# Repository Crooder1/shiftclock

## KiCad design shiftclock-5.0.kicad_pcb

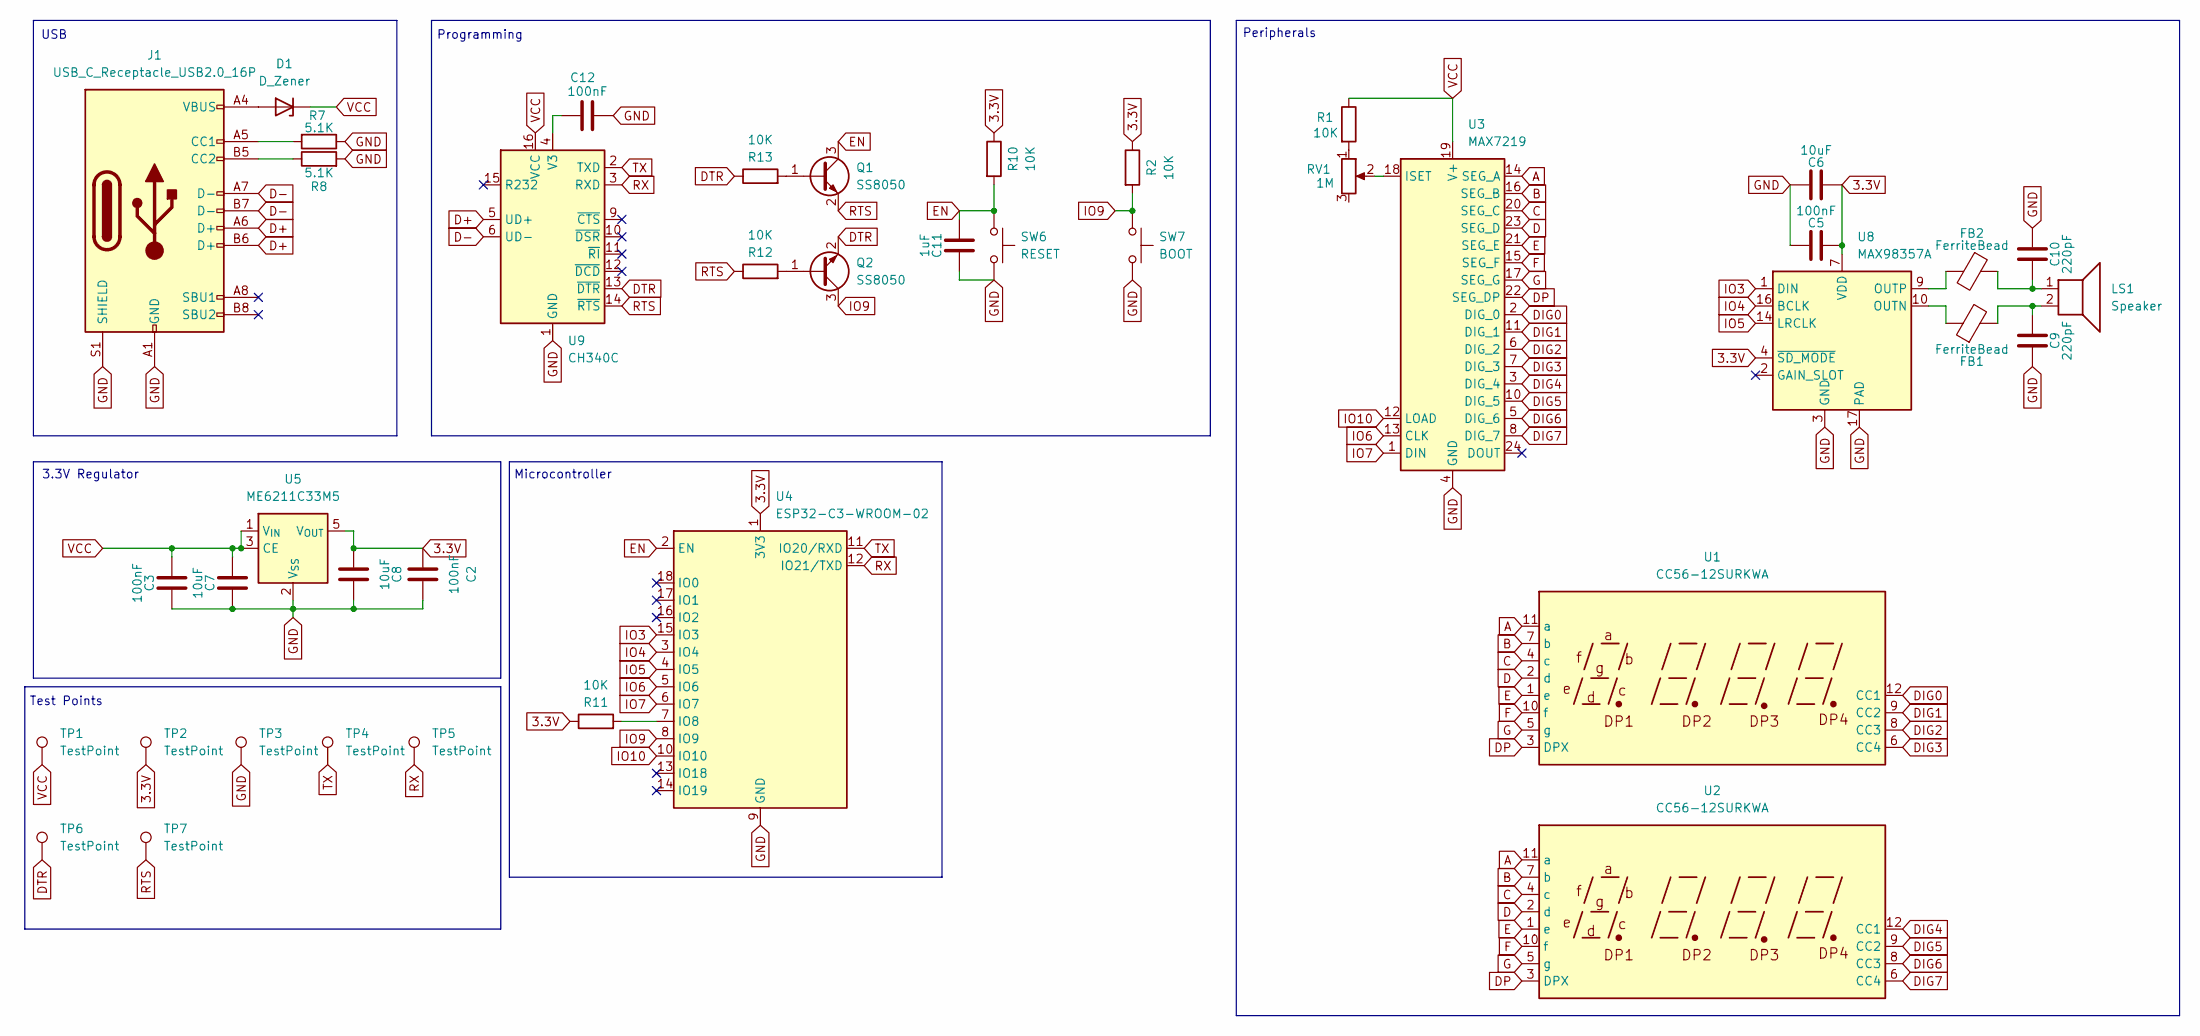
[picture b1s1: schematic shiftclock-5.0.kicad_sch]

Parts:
C2, C3, C5, C12: 100nF; C_1206_3216Metric_Pad1.33x1.80mm_HandSolder
C6, C7, C8: 10uF; C_1206_3216Metric_Pad1.33x1.80mm_HandSolder
C9, C10: 220pF; C_1206_3216Metric_Pad1.33x1.80mm_HandSolder
C11: 1uF; C_1206_3216Metric_Pad1.33x1.80mm_HandSolder
D1: D_Zener; D_MiniMELF
FB1, FB2: FerriteBead; R_1206_3216Metric_Pad1.30x1.75mm_HandSolder
J1: USB_C_Receptacle_USB2.0_16P; USB_C_Receptacle_Palconn_UTC16-G
LS1: Speaker; PinHeader_2x01_P1.00mm_Vertical_SMD
Q1, Q2: SS8050; SOT-23
R1, R2, R10, R11, R12, R13: 10K; R_1206_3216Metric_Pad1.30x1.75mm_HandSolder
R7, R8: 5.1K; R_1206_3216Metric_Pad1.30x1.75mm_HandSolder
RV1: 1M; Potentiometer_Runtron_RM-065_Vertical
SW6: RESET; SW_Tactile_SPST_NO_Straight_CK_PTS636Sx25SMTRLFS
SW7: BOOT; SW_Tactile_SPST_NO_Straight_CK_PTS636Sx25SMTRLFS
TP1, TP2, TP3, TP4, TP5, TP6, TP7: TestPoint; TestPoint_Pad_2.0x2.0mm
U1, U2: CC56-12SURKWA; CA56-12SURKWA
U3: MAX7219; SOIC-24W_7.5x15.4mm_P1.27mm
U4: ESP32-C3-WROOM-02
U5: ME6211C33M5; SOT-23-5
U8: MAX98357A; TQFN-16-1EP_3x3mm_P0.5mm_EP1.23x1.23mm
U9: CH340C; SOIC-16_3.9x9.9mm_P1.27mm

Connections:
3.3V: C2.1, C5.1, C6.1, C8.1, R2.1, R10.1, R11.1, TP2.1, U4.1 (3V3), U5.5 (V_{OUT}), U8.4 (~SD_MODE), U8.7 (VDD), U8.8 (VDD)
A: U1.11 (a), U2.11 (a), U3.14 (SEG_A)
B: U1.7 (b), U2.7 (b), U3.16 (SEG_B)
C: U1.4 (c), U2.4 (c), U3.20 (SEG_C)
D: U1.2 (d), U2.2 (d), U3.23 (SEG_D)
D+: J1.A6 (D+), J1.B6 (D+), U9.5 (UD+)
D-: J1.A7 (D-), J1.B7 (D-), U9.6 (UD-)
DIG0: U1.12 (CC1), U3.2 (DIG_0)
DIG1: U1.9 (CC2), U3.11 (DIG_1)
DIG2: U1.8 (CC3), U3.6 (DIG_2)
DIG3: U1.6 (CC4), U3.7 (DIG_3)
DIG4: U2.12 (CC1), U3.3 (DIG_4)
DIG5: U2.9 (CC2), U3.10 (DIG_5)
DIG6: U2.8 (CC3), U3.5 (DIG_6)
DIG7: U2.6 (CC4), U3.8 (DIG_7)
DP: U1.3 (DPX), U2.3 (DPX), U3.22 (SEG_DP)
DTR: Q2.2 (E), R13.1, TP6.1, U9.13 (~DTR)
E: U1.1 (e), U2.1 (e), U3.21 (SEG_E)
EN: C11.1, Q1.3 (C), R10.2, SW6.1, U4.2 (EN)
F: U1.10 (f), U2.10 (f), U3.15 (SEG_F)
G: U1.5 (g), U2.5 (g), U3.17 (SEG_G)
GND: C2.2, C3.2, C5.2, C6.2, C7.2, C8.2, C9.1, C10.2, C11.2, C12.2, J1.A1 (GND), J1.A12 (GND), J1.B1 (GND), J1.B12 (GND), J1.S1 (SHIELD), R7.1, R8.2, SW6.2, SW7.2, TP3.1, U3.4 (GND), U3.9 (GND), U4.9 (GND), U4.19 (GND), U5.2 (V_{SS}), U8.3 (GND), U8.11 (GND), U8.15 (GND), U8.17 (PAD), U9.1 (GND)
IO3: U4.15 (IO3), U8.1 (DIN)
IO4: U4.3 (IO4), U8.16 (BCLK)
IO5: U4.4 (IO5), U8.14 (LRCLK)
IO6: U3.13 (CLK), U4.5 (IO6)
IO7: U3.1 (DIN), U4.6 (IO7)
IO9: Q2.3 (C), R2.2, SW7.1, U4.8 (IO9)
IO10: U3.12 (LOAD), U4.10 (IO10)
unnamed: C9.2, FB1.2, LS1.2
unnamed: C10.1, FB2.1, LS1.1
unnamed: D1.2 (A), J1.A4 (VBUS), J1.A9 (VBUS), J1.B4 (VBUS), J1.B9 (VBUS)
unnamed: J1.A5 (CC1), R7.2
unnamed: J1.B5 (CC2), R8.1
unnamed: Q1.1 (B), R13.2
unnamed: Q2.1 (B), R12.2
unnamed: R1.2, RV1.1
unnamed: RV1.2, U3.18 (ISET)
unnamed: R11.2, U4.7 (IO8)
unnamed: FB1.1, U8.10 (OUTN)
unnamed: FB2.2, U8.9 (OUTP)
unnamed: C12.1, U9.4 (V3)
RTS: Q1.2 (E), R12.1, TP7.1, U9.14 (~RTS)
RX: TP5.1, U4.12 (IO21/TXD), U9.3 (RXD)
TX: TP4.1, U4.11 (IO20/RXD), U9.2 (TXD)
VCC: C3.1, C7.1, D1.1 (K), R1.1, TP1.1, U3.19 (V+), U5.1 (V_{IN}), U5.3 (CE), U9.16 (VCC)

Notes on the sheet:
3.3V Regulator
Test Points
Programming
Peripherals
USB
Microcontroller

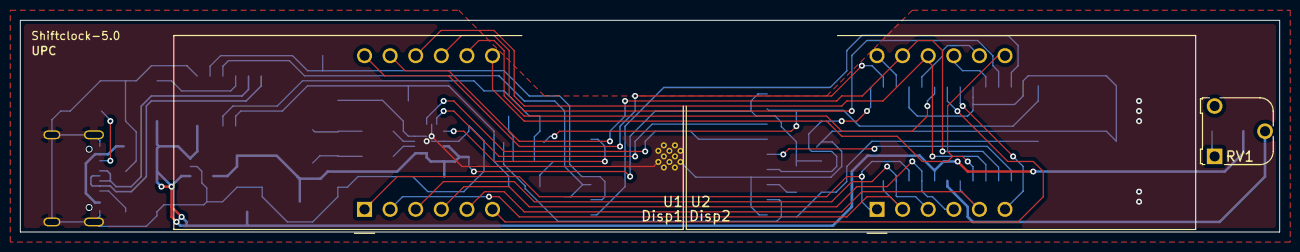
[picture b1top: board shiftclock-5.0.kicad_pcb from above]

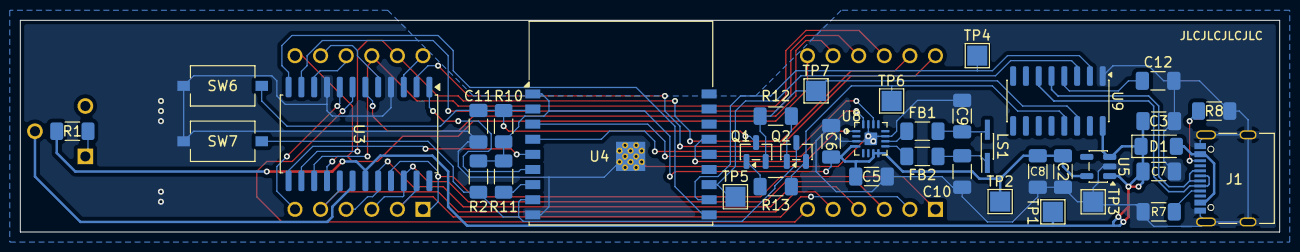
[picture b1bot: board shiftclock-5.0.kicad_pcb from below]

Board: 4 copper layers, 124.9 x 21.0 mm, 42 parts (39 on the bottom side), 46 nets.

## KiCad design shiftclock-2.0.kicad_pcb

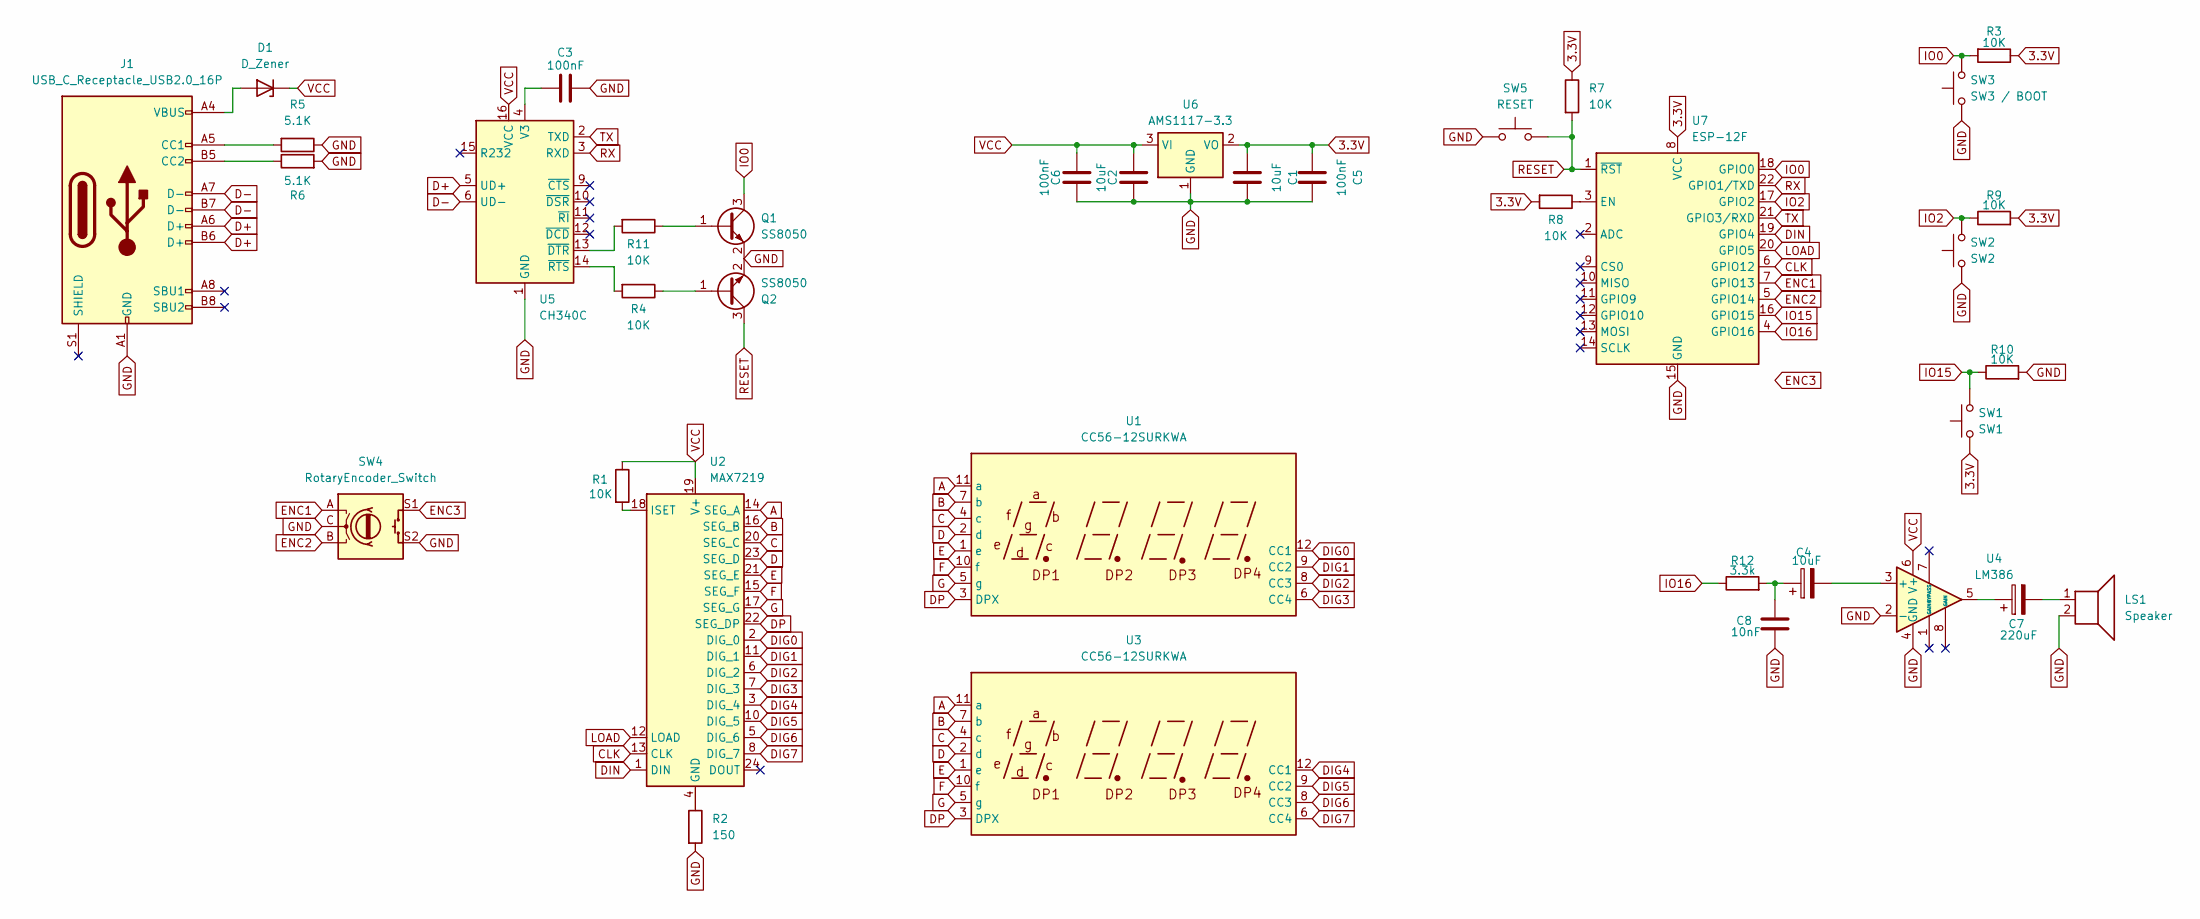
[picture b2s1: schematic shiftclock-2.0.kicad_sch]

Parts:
C1, C2: 10uF; C_1206_3216Metric_Pad1.33x1.80mm_HandSolder
C3, C5, C6: 100nF; C_1206_3216Metric_Pad1.33x1.80mm_HandSolder
C4: 10uF; CP_Elec_4x5.4
C7: 220uF; CP_Elec_6.3x7.7
C8: 10nF; C_1206_3216Metric_Pad1.33x1.80mm_HandSolder
D1: D_Zener; D_MiniMELF
J1: USB_C_Receptacle_USB2.0_16P; USB_C_Receptacle_Palconn_UTC16-G
LS1: Speaker; PinHeader_1x02_P2.54mm_Vertical
Q1, Q2: SS8050; SOT-23
R1, R3, R4, R7, R8, R9, R10, R11: 10K; R_1206_3216Metric_Pad1.30x1.75mm_HandSolder
R2: 150; R_1206_3216Metric_Pad1.30x1.75mm_HandSolder
R5, R6: 5.1K; R_1206_3216Metric_Pad1.30x1.75mm_HandSolder
R12: 3.3k; R_1206_3216Metric_Pad1.30x1.75mm_HandSolder
SW1: SW1; SW_PUSH_6mm_H5mm
SW2: SW2; SW_PUSH_6mm_H5mm
SW3: SW3 / BOOT; SW_PUSH_6mm_H5mm
SW4: RotaryEncoder_Switch; RotaryEncoder_Alps_EC12E-Switch_Vertical_H20mm_CircularMoun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
SW5: RESET; SW_Tactile_SPST_NO_Straight_CK_PTS636Sx25SMTRLFS
U1, U3: CC56-12SURKWA; CA56-12SURKWA
U2: MAX7219; SOIC-24W_7.5x15.4mm_P1.27mm
U4: LM386; SOIC-8_3.9x4.9mm_P1.27mm
U5: CH340C; SOIC-16_3.9x9.9mm_P1.27mm
U6: AMS1117-3.3; SOT-223-3_TabPin2
U7: ESP-12F; ESP-12E

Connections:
3.3V: C1.1, C5.1, R3.1, R7.1, R8.2, R9.2, SW1.2, U6.2 (VO), U7.8 (VCC)
A: U1.11 (a), U2.14 (SEG_A), U3.11 (a)
B: U1.7 (b), U2.16 (SEG_B), U3.7 (b)
C: U1.4 (c), U2.20 (SEG_C), U3.4 (c)
CLK: U2.13 (CLK), U7.6 (GPIO12)
D: U1.2 (d), U2.23 (SEG_D), U3.2 (d)
D+: J1.A6 (D+), J1.B6 (D+), U5.5 (UD+)
D-: J1.A7 (D-), J1.B7 (D-), U5.6 (UD-)
DIG0: U1.12 (CC1), U2.2 (DIG_0)
DIG1: U1.9 (CC2), U2.11 (DIG_1)
DIG2: U1.8 (CC3), U2.6 (DIG_2)
DIG3: U1.6 (CC4), U2.7 (DIG_3)
DIG4: U2.3 (DIG_4), U3.12 (CC1)
DIG5: U2.10 (DIG_5), U3.9 (CC2)
DIG6: U2.5 (DIG_6), U3.8 (CC3)
DIG7: U2.8 (DIG_7), U3.6 (CC4)
DIN: U2.1 (DIN), U7.19 (GPIO4)
DP: U1.3 (DPX), U2.22 (SEG_DP), U3.3 (DPX)
E: U1.1 (e), U2.21 (SEG_E), U3.1 (e)
ENC1: SW4.A, U7.7 (GPIO13)
ENC2: SW4.B, U7.5 (GPIO14)
ENC3: SW4.S1
F: U1.10 (f), U2.15 (SEG_F), U3.10 (f)
G: U1.5 (g), U2.17 (SEG_G), U3.5 (g)
GND: C1.2, C2.2, C3.2, C5.2, C6.2, C8.1, J1.A1 (GND), J1.A12 (GND), J1.B1 (GND), J1.B12 (GND), LS1.2, Q1.2 (E), Q2.2 (E), R2.2, R5.1, R6.2, R10.2, SW2.2, SW3.2, SW4.C, SW4.S2, SW5.1, U4.2 (-), U4.4 (GND), U5.1 (GND), U6.1 (GND), U7.15 (GND)
IO0: Q1.3 (C), R3.2, SW3.1, U7.18 (GPIO0)
IO2: R9.1, SW2.1, U7.17 (GPIO2)
IO15: R10.1, SW1.1, U7.16 (GPIO15)
IO16: R12.1, U7.4 (GPIO16)
LOAD: U2.12 (LOAD), U7.20 (GPIO5)
unnamed: C4.1, C8.2, R12.2
unnamed: C7.1, U4.5
unnamed: C7.2, LS1.1
unnamed: D1.2 (A), J1.A4 (VBUS), J1.A9 (VBUS), J1.B4 (VBUS), J1.B9 (VBUS)
unnamed: J1.A5 (CC1), R5.2
unnamed: J1.B5 (CC2), R6.1
unnamed: Q1.1 (B), R11.1
unnamed: Q2.1 (B), R4.1
unnamed: R2.1, U2.4 (GND), U2.9 (GND)
unnamed: R1.2, U2.18 (ISET)
unnamed: C4.2, U4.3 (+)
unnamed: C3.1, U5.4 (V3)
unnamed: R11.2, U5.13 (~DTR)
unnamed: R4.2, U5.14 (~RTS)
unnamed: R8.1, U7.3 (EN)
RESET: Q2.3 (C), R7.2, SW5.2, U7.1 (~RST)
RX: U5.3 (RXD), U7.22 (GPIO1/TXD)
TX: U5.2 (TXD), U7.21 (GPIO3/RXD)
VCC: C2.1, C6.1, D1.1 (K), R1.1, U2.19 (V+), U4.6 (V+), U5.16 (VCC), U6.3 (VI)

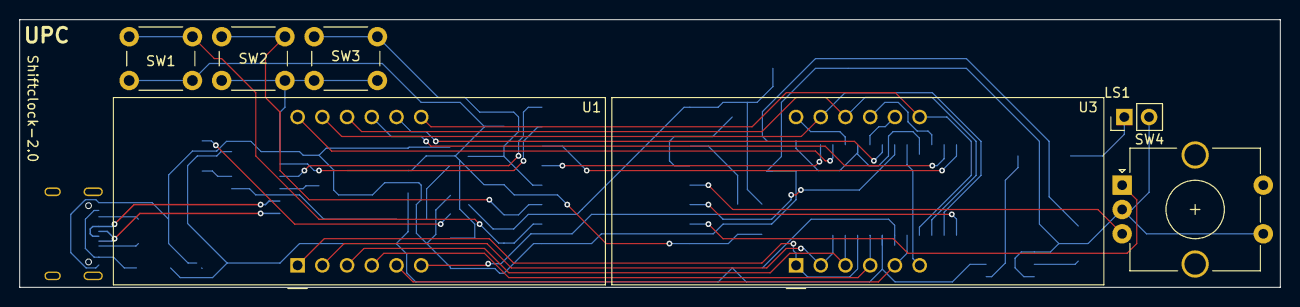
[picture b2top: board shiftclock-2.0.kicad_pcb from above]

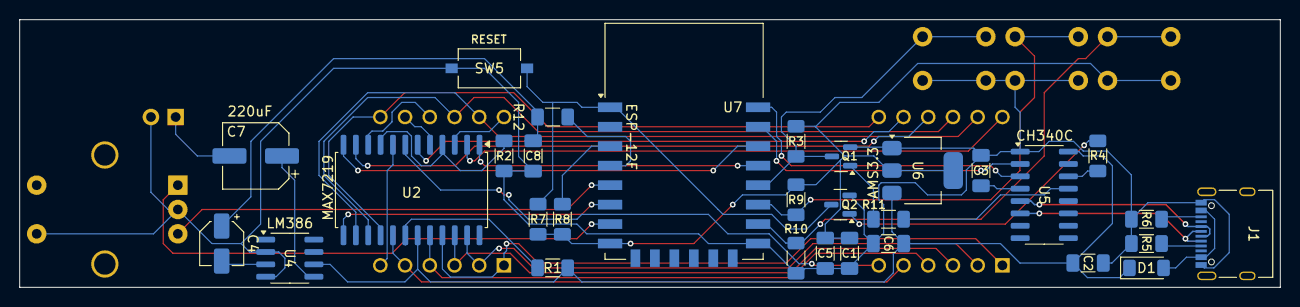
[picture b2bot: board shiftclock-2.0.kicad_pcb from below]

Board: 4 copper layers, 129.5 x 27.5 mm, 37 parts (30 on the bottom side), 48 nets.

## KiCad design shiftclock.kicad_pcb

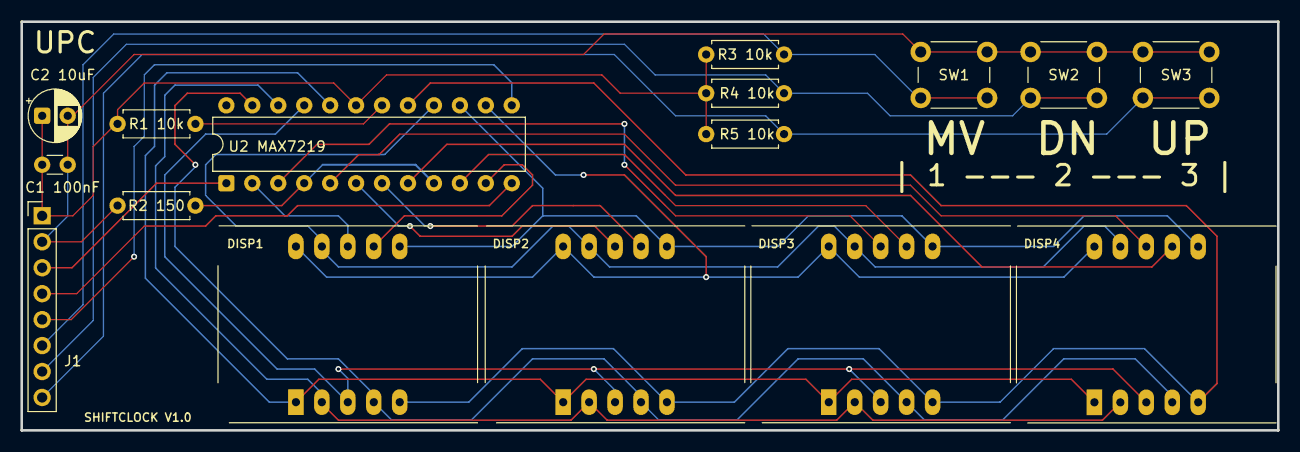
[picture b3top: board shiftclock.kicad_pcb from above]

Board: 4 copper layers, 123.0 x 40.0 mm, 16 parts (0 on the bottom side), 26 nets.

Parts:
7C1, 7C2, 7C3, 7C4: 2x7SegmentCC
C1 100nF: C; C_Disc_D3.0mm_W1.6mm_P2.50mm
C2 10uF: C_Polarized; CP_Radial_D5.0mm_P2.50mm
J1: Conn_01x08_Pin; PinHeader_1x08_P2.54mm_Vertical
R1 10k, R3 10k, R4 10k, R5 10k: 10k; R_Axial_DIN0207_L6.3mm_D2.5mm_P7.62mm_Horizontal
R2 150: 150; R_Axial_DIN0207_L6.3mm_D2.5mm_P7.62mm_Horizontal
SW1, SW2, SW3: SW_Push; SW_PUSH_6mm_H5mm
U2 MAX7219: MAX7219; DIP-24_W7.62mm

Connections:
A: 7C1.10 (A), 7C2.10 (A), 7C3.10 (A), 7C4.10 (A), U2 MAX7219.14 (SEG_A)
B: 7C1.9 (B), 7C2.9 (B), 7C3.9 (B), 7C4.9 (B), U2 MAX7219.16 (SEG_B)
C: 7C1.1 (C), 7C2.1 (C), 7C3.1 (C), 7C4.1 (C), U2 MAX7219.20 (SEG_C)
CLK: J1.5, U2 MAX7219.13 (CLK)
D: 7C1.4 (D), 7C2.4 (D), 7C3.4 (D), 7C4.4 (D), U2 MAX7219.23 (SEG_D)
DIG0: 7C1.8 (CC1), U2 MAX7219.2 (DIG_0)
DIG1: 7C1.7 (CC2), U2 MAX7219.11 (DIG_1)
DIG2: 7C2.8 (CC1), U2 MAX7219.6 (DIG_2)
DIG3: 7C2.7 (CC2), U2 MAX7219.7 (DIG_3)
DIG4: 7C3.8 (CC1), U2 MAX7219.3 (DIG_4)
DIG5: 7C3.7 (CC2), U2 MAX7219.10 (DIG_5)
DIG6: 7C4.8 (CC1), U2 MAX7219.5 (DIG_6)
DIG7: 7C4.7 (CC2), U2 MAX7219.8 (DIG_7)
DIN: J1.3, U2 MAX7219.1 (DIN)
DP: 7C1.2 (DP), 7C2.2 (DP), 7C3.2 (DP), 7C4.2 (DP), U2 MAX7219.22 (SEG_DP)
E: 7C1.3 (E), 7C2.3 (E), 7C3.3 (E), 7C4.3 (E), U2 MAX7219.21 (SEG_E)
F: 7C1.6 (F), 7C2.6 (F), 7C3.6 (F), 7C4.6 (F), U2 MAX7219.15 (SEG_F)
G: 7C1.5 (G), 7C2.5 (G), 7C3.5 (G), 7C4.5 (G), U2 MAX7219.17 (SEG_G)
GND: C1 100nF.2, C2 10uF.2, J1.2, R2 150.2, SW1.1, SW2.1, SW3.1
LOAD: J1.4, U2 MAX7219.12 (LOAD)
unnamed: R2 150.1, U2 MAX7219.4 (GND), U2 MAX7219.9 (GND)
unnamed: R1 10k.2, U2 MAX7219.18 (ISET)
SW1: J1.6, R3 10k.2, SW1.2
SW2: J1.7, R4 10k.2, SW2.2
SW3: J1.8, R5 10k.2, SW3.2
VCC: C1 100nF.1, C2 10uF.1, J1.1, R1 10k.1, R3 10k.1, R4 10k.1, R5 10k.1, U2 MAX7219.19 (V+)

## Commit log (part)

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2026-03-01 Rework Schematic and Begin Layout Connections
2026-04-11 Add Netlist
